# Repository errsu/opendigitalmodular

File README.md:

Open Digital Modular (ODM): Proposal for a Synthesizer Architecture
===================================================================

## What is it?

ODM is an architectural idea that is to be turned into a specification and
a prototype implementation. All this is work in progress. The details can
be found in the [ODM specification document](documentation/ODMSpecification.asc).

## License

See the [licenses page](LICENSES.asc) for details.

## Questions and comments

The main goal of making this public is to get in contact with people for review,
comments, proposals, criticism or laughter. Most valued would be cooperation, and
there is some hope that in the not-so-far future somebody might want to build
actual synthesizers this way.

So, please use the [issue page](https://github.com/errsu/opendigitalmodular/issues)
for public communication or send me a mail for a private conversation.

/errsu

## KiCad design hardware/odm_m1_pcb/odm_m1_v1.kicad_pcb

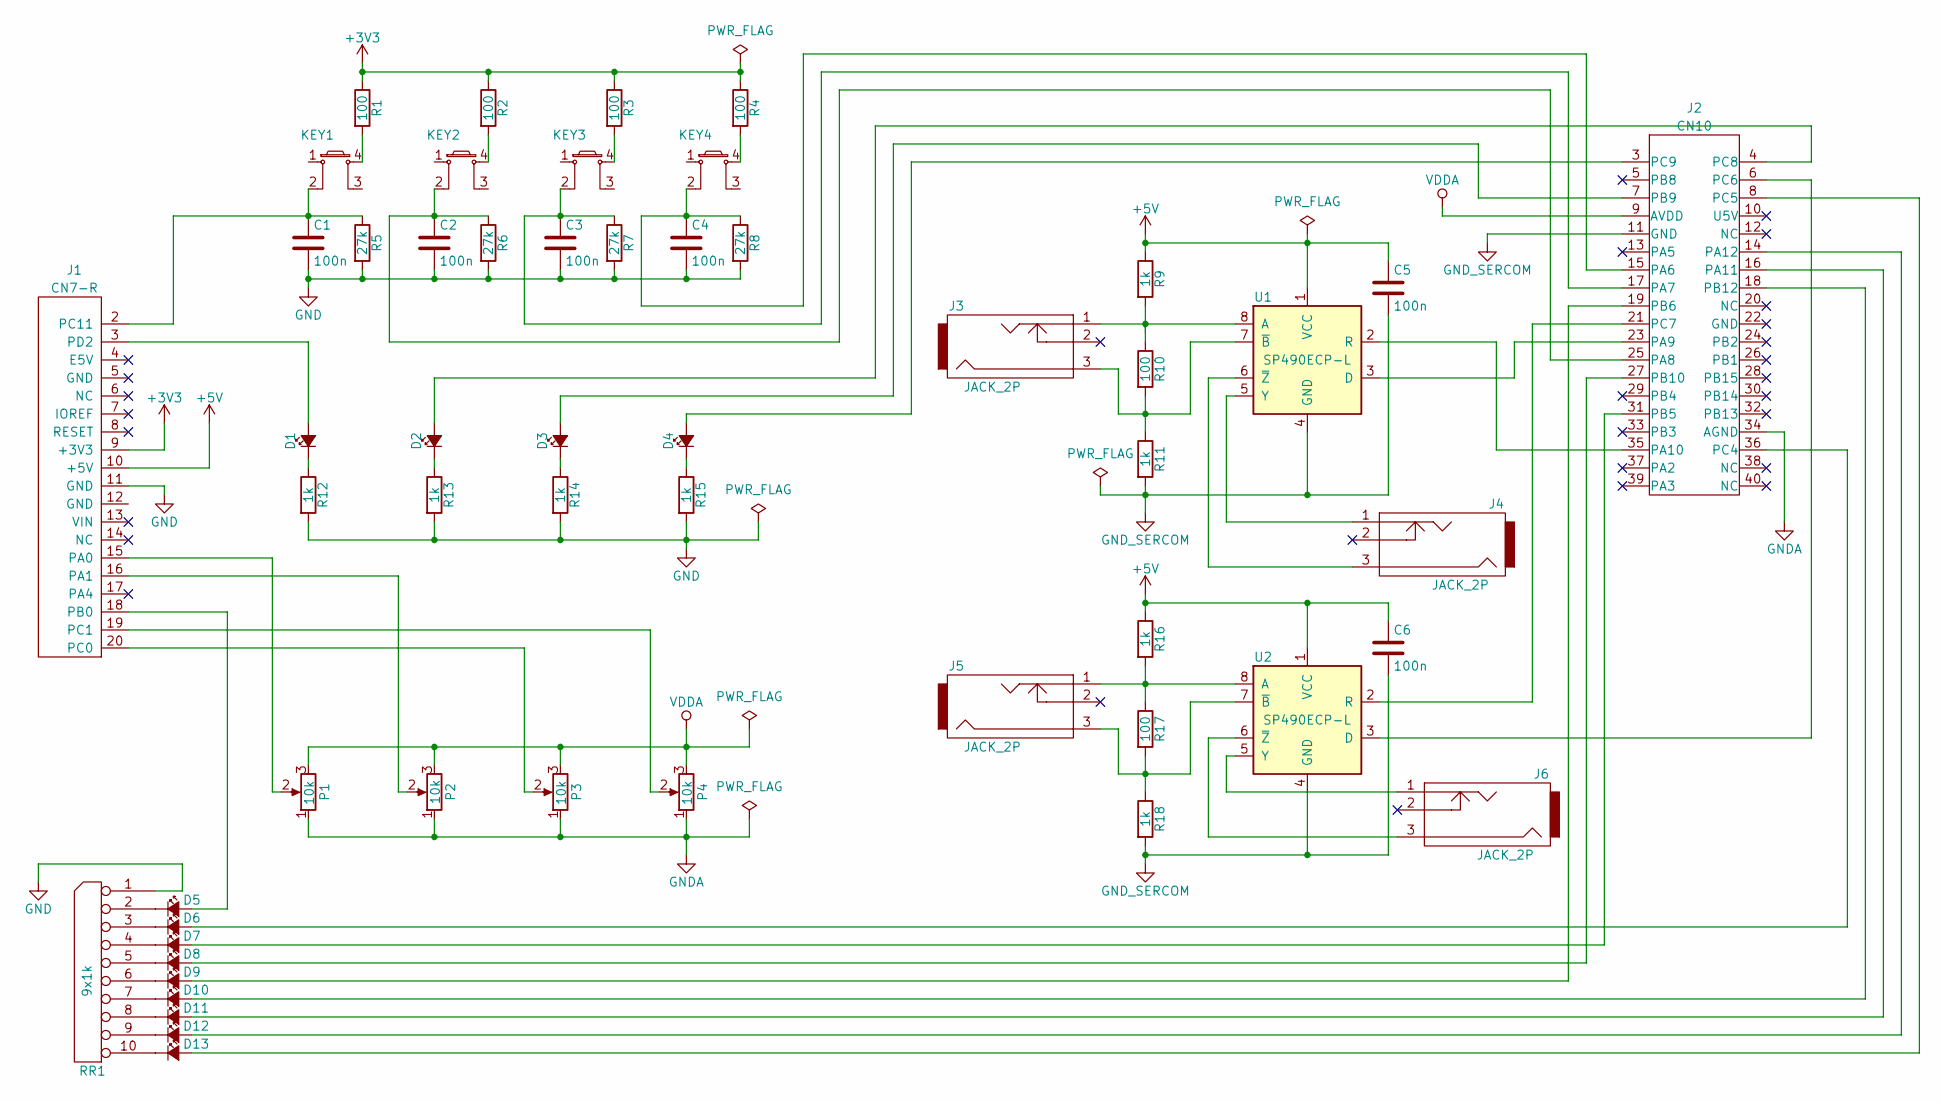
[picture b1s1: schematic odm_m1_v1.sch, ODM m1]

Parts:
C1, C2, C3, C4, C5, C6: 100n; C_Disc_D3_P2.5
D1, D2, D3, D4, D5, D6, D7, D8, D9, D10, D11, D12, D13: Led_Small; LED-3MM
J1: CN7-R; Socket_Strip_Straight_1x20_RS
J2: CN10; Socket_Strip_Straight_2x20_RS
J3, J4, J5, J6: JACK_2P; PHONEJACK_35MM_MONO_VERT
KEY1, KEY2, KEY3, KEY4: SW_PUSH; SW_PUSH_SMALL
P1, P2, P3, P4: 10k; POT_RK09
R1, R2, R3, R4, R10, R17: 100; Resistor_Horizontal_RM7mm
R5, R6, R7, R8: 27k; Resistor_Horizontal_RM7mm
R9, R11, R12, R13, R14, R15, R16, R18: 1k; Resistor_Horizontal_RM7mm
RR1: 9x1k; Resistor_Array_SIP9
U1, U2: SP490ECP-L; DIP-8_W7.62mm

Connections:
+3V3: J1.9 (+3V3), R1.1, R2.1, R3.1, R4.1
+5V: C5.1, C6.1, J1.10 (+5V), R9.1, R16.1, U1.1 (VCC), U2.1 (VCC)
GND: C1.2, C2.2, C3.2, C4.2, J1.11 (GND), R5.2, R6.2, R7.2, R8.2, R12.2, R13.2, R14.2, R15.2, RR1.1 (COM)
GNDA: J2.34 (AGND), P1.1, P2.1, P3.1, P4.1
GND_SERCOM: C5.2, C6.2, J2.11 (GND), R11.2, R18.2, U1.4 (GND), U2.4 (GND)
unnamed: C1.1, J1.2 (PC11), KEY1.2, R5.1
unnamed: C2.1, J2.25 (PA8), KEY2.2, R6.1
unnamed: C3.1, J2.17 (PA7), KEY3.2, R7.1
unnamed: C4.1, J2.15 (PA6), KEY4.2, R8.1
unnamed: D1.1 (K), R12.1
unnamed: D1.2 (A), J1.3 (PD2)
unnamed: D2.1 (K), R13.1
unnamed: D2.2 (A), J2.4 (PC8)
unnamed: D3.1 (K), R14.1
unnamed: D3.2 (A), J2.7 (PB9)
unnamed: D4.1 (K), R15.1
unnamed: D4.2 (A), J2.3 (PC9)
unnamed: D5.1 (K), RR1.2
unnamed: D5.2 (A), J1.18 (PB0)
unnamed: D6.1 (K), RR1.3
unnamed: D6.2 (A), J2.36 (PC4)
unnamed: D7.1 (K), RR1.4
unnamed: D7.2 (A), J2.31 (PB5)
unnamed: D8.1 (K), RR1.5
unnamed: D8.2 (A), J2.27 (PB10)
unnamed: D9.1 (K), RR1.6
unnamed: D9.2 (A), J2.19 (PB6)
unnamed: D10.1 (K), RR1.7
unnamed: D10.2 (A), J2.18 (PB12)
unnamed: D11.1 (K), RR1.8
unnamed: D11.2 (A), J2.16 (PA11)
unnamed: D12.1 (K), RR1.9
unnamed: D12.2 (A), J2.14 (PA12)
unnamed: D13.1 (K), RR1.10
unnamed: D13.2 (A), J2.8 (PC5)
unnamed: J1.15 (PA0), P1.2
unnamed: J1.16 (PA1), P2.2
unnamed: J1.19 (PC1), P4.2
unnamed: J1.20 (PC0), P3.2
unnamed: J2.6 (PC6), U2.3 (D)
unnamed: J2.21 (PC7), U2.2 (R)
unnamed: J2.23 (PA9), U1.3 (D)
unnamed: J2.35 (PA10), U1.2 (R)
unnamed: J3.1, R9.2, R10.1, U1.8 (A)
unnamed: J3.3, R10.2, R11.1, U1.7 (~B~)
unnamed: J4.1, U1.5 (Y)
unnamed: J4.3, U1.6 (~Z~)
unnamed: J5.1, R16.2, R17.1, U2.8 (A)
unnamed: J5.3, R17.2, R18.1, U2.7 (~B~)
unnamed: J6.1, U2.5 (Y)
unnamed: J6.3, U2.6 (~Z~)
unnamed: KEY1.4, R1.2
unnamed: KEY2.4, R2.2
unnamed: KEY3.4, R3.2
unnamed: KEY4.4, R4.2
VDDA: J2.9 (AVDD), P1.3, P2.3, P3.3, P4.3

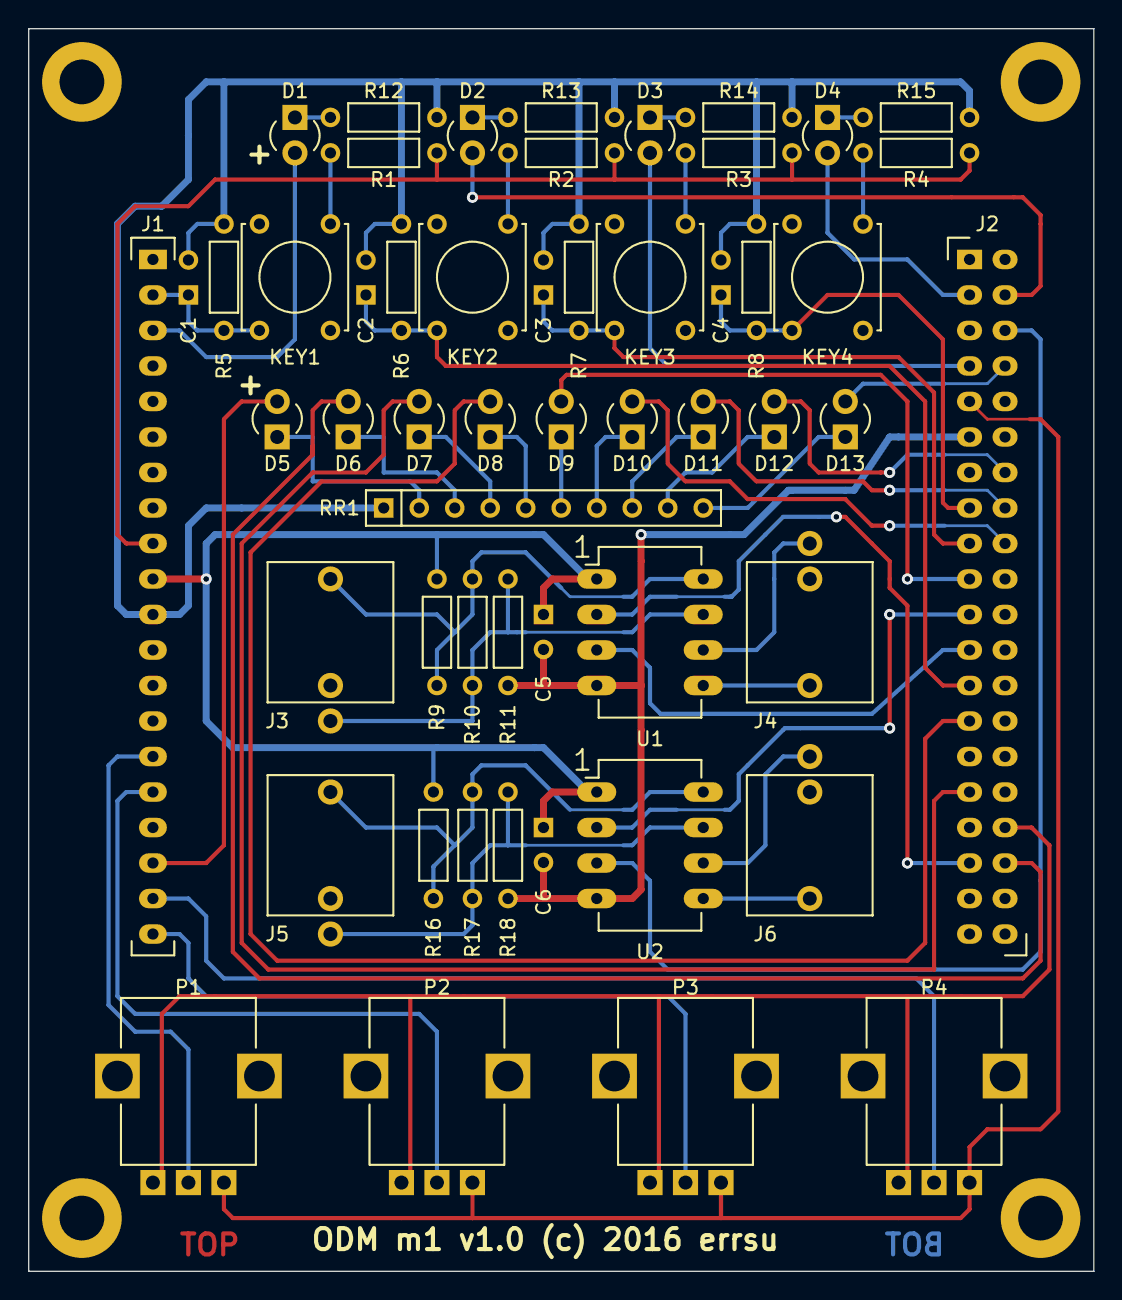
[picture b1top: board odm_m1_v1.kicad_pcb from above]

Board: 2 copper layers, 76.2 x 88.9 mm, 54 parts (0 on the bottom side), 56 nets.

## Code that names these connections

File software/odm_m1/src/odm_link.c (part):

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#define RX_DEBOUNCING 96*500 // 50 ms

//--------------------------------------------------------------------------------------
// TX: PA9 aka. D8, CN10.pin21   RX: PA10 aka. D2, CN10.pin33

odm_link_trx_t ODM_LINK_A =
{
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};

//--------------------------------------------------------------------------------------
// TX: PC6, CN10.pin4    RX: PC7 aka. D9, CN10.pin19

odm_link_trx_t ODM_LINK_B =
{
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
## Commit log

2018-05-10 add images for specification
2018-05-11 ODM specification first draft
    - as derived from ipad sketches
2018-05-11 add some prototype board images
2018-05-12 have a cleaner folder structure
2018-05-12 add the ODM m1 PCB prototype
2018-05-13 add the ODM m1 prototype software
2018-05-15 a few corrections (spelling) and clarifications to the spec
2018-05-18 updated the MIDI part of ODM link
    - 32 bit UDB MIDI idea does not work as there is no easy
    way to introduce a 4 byte frame into the stream
    - after some thinking, the use of sysex over ODM link
    appears to be both useless and counterproductive,
    the host link eliminates the need for sysex
2018-05-18 add some details to the ODM host protocol chapter
    - thanks Raphael for pointing out the pots vs. restore problem
2018-05-19 make it clear to use stereo cables for ODM link
    We have to sacrifice the mono cables for electromagnetic compatibility.
    Somehow I knew it all the time, that I can't leave it without
    shielding, just didn't want to face the truth. So, sadly,
    the mono cables of analog patching can't be used.

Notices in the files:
software/odm_m1/src/odm_link.c:
(C) Copyright 2015-2018 Errsu
Licensed under the Apache License, Version 2.0 (the "License");
hardware/odm_m1_pcb/odm_m1_v1.kicad_pcb:
(c) copyright 2016 errsu
ODM m1 v1.0 (c) 2016 errsu
